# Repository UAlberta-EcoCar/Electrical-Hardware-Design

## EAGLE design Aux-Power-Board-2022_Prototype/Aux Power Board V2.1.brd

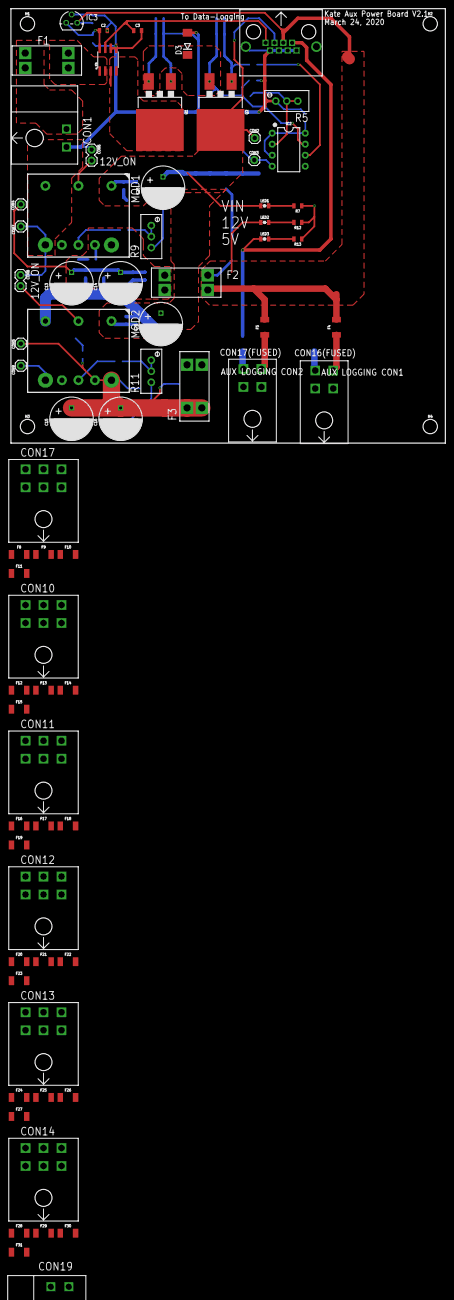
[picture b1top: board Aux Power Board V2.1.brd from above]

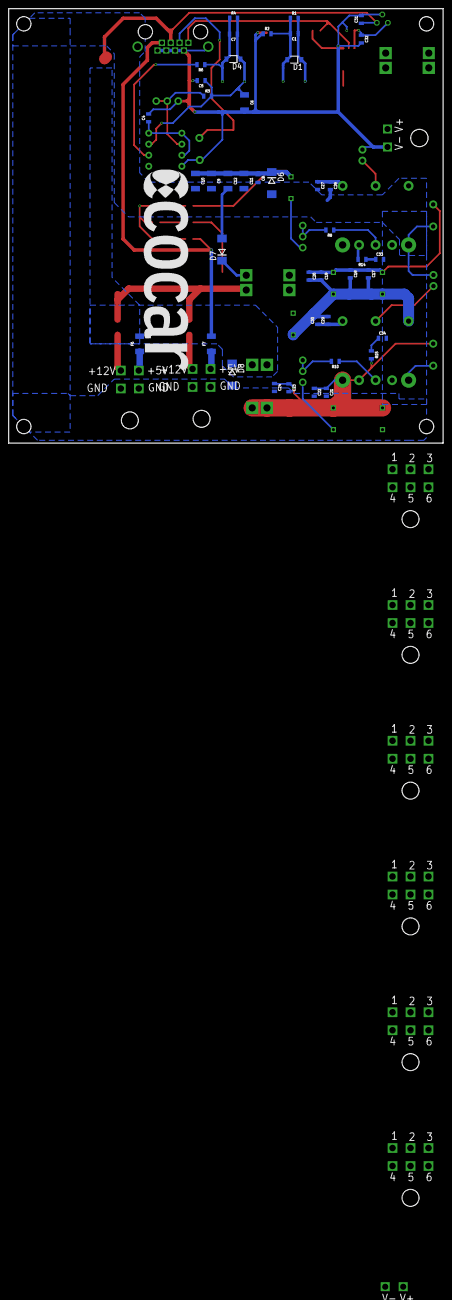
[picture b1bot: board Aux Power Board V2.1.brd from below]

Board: 2 copper layers, 100.0 x 100.0 mm, 120 parts (43 on the bottom side), 56 nets.

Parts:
C1, C2, C5, C7, C8, C17, C21: 0.1uF; 0805
C3: 1nF; 0805
C4, C31, C32: 1uF; 0805
C6, C9, C10, C11, C12: 10uF; 1210
C13, C14, C15, C16, C25, C26: 220uF; CAPACITOR_220UF_63V
C18, C19, C20, C22, C23, C24: 10uF; 0805
C27, C29: 1nF/50V; 0805
C28, C30: 1uF/50V; 0805
C33, C34: 0805
CON1, CON19: TE_2-PIN
CON2, CON3, CON4, CON5, CON7, CON9: 1X01
CON6, CON8: 1X02
CON10, CON11, CON12, CON13, CON14, CON17: TE_6-PIN
CON16(FUSED), CON17(FUSED): TE_4-PIN
CON18: RJ45
D1, D4: BZT52HC10WF-7; SOD123FL
D3, D6: SMBJ22A; DO214AA
D7: SMBJ12A; DO214AA
D8: SMBJ5.0A; DO214AA
F1, F2, F3: 7.5A; FUSEHOLDER_VERTICAL
F4, F5, F6, F7, F8, F9, F10, F11, F12, F13, F14, F15, F16, F17, F18, F19, F20, F21, F22, F23, F24, F25, F26, F27, F28, F29, F30, F31: 1210
H1, H2, H3, H4: STAND-OFF
IC1: CURRENT-SENSOR_ACS723; SOIC8
IC2: OP-AMP_LM10; DIP08
IC3: LINEAR-REGULATOR_LP2950; TO92
LED1, LED2, LED3: RED; 0805_LED
MOD1, MOD2: i3A; CONVERTER_I3A
Q1, Q2: TO-263/D2PAK
R1, R3, R4: 100k; 0805
R2, R6: 2.7k; 0805
R5, R9, R11: 10k; TRIMPOT
R7: 3.9k; 0805
R8: 1.6k; 0805
R10: 8.2k; 0805
R12: 2k; 0805
R13: 560; 0805
R14, R15: 0805
U$7: ECOCAR_LOGO; ECOCAR_LOGO_2018

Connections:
5V: CON18.7, CON19.1, D8.C, F3.3, F3.4, F6.2, F7.2, F8.2, F9.2, F12.2, F13.2, F16.2, F17.2, F20.2, F21.2, F24.2, F25.2, F28.2, F29.2, LED3.1
5V_LINEAR: C2.1, C32.1, IC1.8, IC3.3
5V_PRE_FUSE: C15.+, C16.+, C21.1, C22.1, C23.1, C24.1, CON5.1, F3.1, F3.2, MOD2.7, MOD2.8, R15.2
12V: C31.1, CON18.5, D7.C, F2.3, F2.4, F4.2, F5.2, F10.2, F11.2, F14.2, F15.2, F18.2, F19.2, F22.2, F23.2, F26.2, F27.2, F30.2, F31.2, IC3.1, LED2.1
12V_PRE_FUSE: C13.+, C14.+, C17.1, C18.1, C19.1, C20.1, CON4.1, F2.1, F2.2, MOD1.7, MOD1.8, R14.2
!OUTPUT_ENABLED: IC2.6, R6.2
+5V: CON17.6, F9.1
+5V1: CON10.6, F13.1
+5V2: CON11.6, F17.1
+5V3: CON12.6, F21.1
+5V4: CON13.6, F25.1
+5V5: CON14.6, F29.1
+12V: CON17.1, F11.1
+12V1: CON10.1, F15.1
+12V2: CON11.1, F19.1
+12V3: CON12.1, F23.1
+12V4: CON13.1, F27.1
+12V5: CON14.1, F31.1
BATTERY_IN: CON1.1, F1.1, F1.2
CURRENT_SENSOR_IN: F1.3, F1.4, IC1.1, IC1.2
CURRENT_SENSOR_OUT: IC1.3, IC1.4, Q1.2
GND: C2.2, C3.2, C4.2, C5.2, C6.2, C8.2, C9.2, C10.2, C11.2, C12.2, C13.-, C14.-, C15.-, C16.-, C17.2, C18.2, C19.2, C20.2, C21.2, C22.2, C23.2, C24.2, C25.-, C26.-, C27.2, C28.2, C29.2, C30.2, C31.2, C32.2, C33.2, C34.2, CON1.2, CON3.1, CON6.1, CON7.1, CON8.1, CON9.1, CON10.2, CON10.5, CON11.2, CON11.5, CON12.2, CON12.5, CON13.2, CON13.5, CON14.2, CON14.5, CON16(FUSED).3, CON16(FUSED).4, CON17.2, CON17.5, CON17(FUSED).3, CON17(FUSED).4, CON18.2, CON18.4, CON18.6, CON18.8, CON18.9, CON18.10, CON19.2, D3.A, D6.A, D7.A, D8.A, IC1.5, IC1.6, IC2.4, IC3.2, MOD1.3, MOD1.4, MOD2.3, MOD2.4, R2.1, R5.1, R7.1, R9.3, R11.3, R12.1, R13.1
HALL_CURRENT: C3.1, CON18.1, IC1.7
unnamed: CON16(FUSED).2, F6.1
unnamed: CON16(FUSED).1, F4.1
unnamed: MOD1.6, R8.1
unnamed: LED1.2, R7.2
unnamed: C4.1, IC2.1, IC2.3, IC2.8
unnamed: IC2.2, R3.1, R5.2, R5.3
unnamed: R8.2, R9.1, R9.2
unnamed: C7.2, D4.A, Q2.1, R4.1, R6.1
unnamed: C33.1, R14.1
unnamed: CON17(FUSED).1, F5.1
unnamed: MOD2.6, R10.1
unnamed: CON17(FUSED).2, F7.1
unnamed: LED3.2, R13.2
unnamed: C1.2, D1.A, Q1.1, R1.1, R2.2
unnamed: C34.1, R15.1
unnamed: CON10.3, F14.1
unnamed: LED2.2, R12.2
unnamed: CON17.3, F10.1
unnamed: CON10.4, F12.1
unnamed: CON17.4, F8.1
unnamed: CON11.3, F18.1
unnamed: CON11.4, F16.1
unnamed: CON12.3, F22.1
unnamed: CON12.4, F20.1
unnamed: CON13.3, F26.1
unnamed: R10.2, R11.1, R11.2
unnamed: CON13.4, F24.1
unnamed: CON14.3, F30.1
unnamed: CON14.4, F28.1
unnamed: CON6.2, MOD1.2
unnamed: CON8.2, MOD2.2
REVERSE_PROT_OUT: C1.1, C5.1, C6.1, C7.1, D1.C, D3.C, D4.C, IC2.7, Q1.3, Q2.3, R1.2, R3.2, R4.2
VIN: C8.1, C9.1, C10.1, C11.1, C12.1, C25.+, C26.+, C27.1, C28.1, C29.1, C30.1, CON2.1, CON18.3, D6.C, LED1.1, MOD1.1, MOD2.1, Q2.2

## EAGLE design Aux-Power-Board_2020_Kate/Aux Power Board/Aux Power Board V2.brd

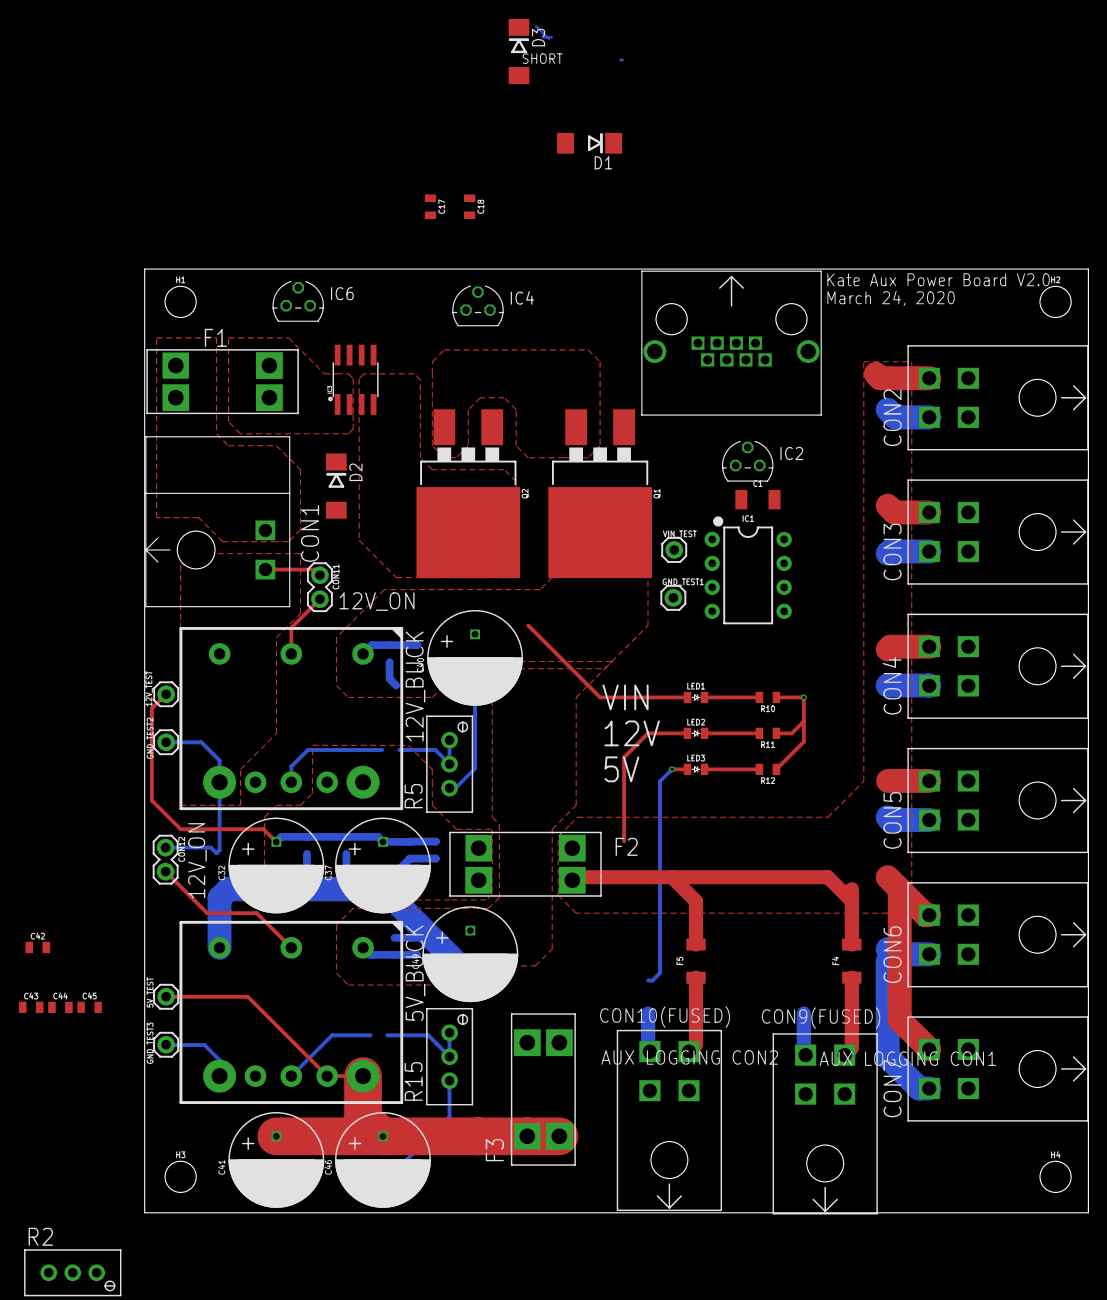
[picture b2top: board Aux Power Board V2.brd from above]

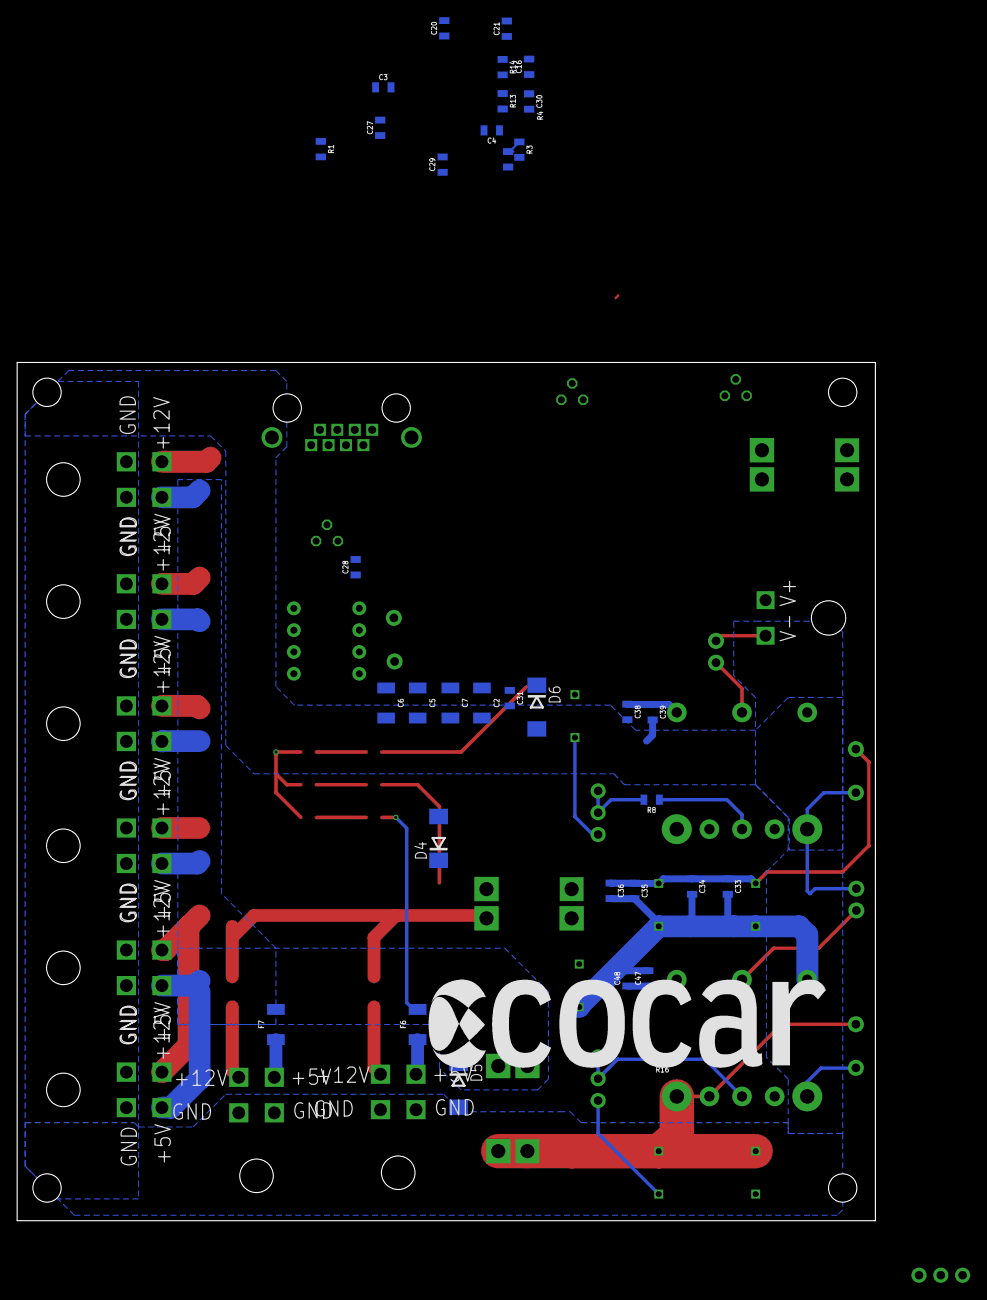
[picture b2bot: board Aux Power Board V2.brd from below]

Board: 2 copper layers, 100.0 x 100.0 mm, 96 parts (35 on the bottom side), 32 nets.

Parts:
5V_BUCK, 12V_BUCK: i3A; CONVERTER_I3A
5V_TEST, 12V_TEST: 1X01
AUX_LOGGING: RJ45
C1, C2, C5, C6, C7: 10uF; 1210
C3, C4, C16, C21: 1uF; 0805
C17, C20, C27, C28, C29, C30, C31, C33, C42: 0.1uF; 0805
C18: 1nF; 0805
C32, C37, C40, C41, C46, C49: 220uF; CAPACITOR_220UF_63V
C34, C35, C36, C43, C44, C45: 10uF; 0805
C38, C47: 1nF/50V; 0805
C39, C48: 1uF/50V; 0805
CON1: TE_2-PIN
CON2, CON3, CON4, CON5, CON6, CON7, CON9(FUSED), CON10(FUSED): TE_4-PIN
CON11, CON12: 1X02
D1, D3, D4: SMBJ12CA; DO214AA
D2, D6: SMBJ22CA; DO214AA
D5: SMBJ5.0CA; DO214AA
F1, F2, F3: 7.5A; FUSEHOLDER_VERTICAL
F4, F5, F6, F7: 1210
GND_TEST1, GND_TEST2, GND_TEST3: 1X01
H1, H2, H3, H4: STAND-OFF
IC1: OP-AMP_LM10; DIP08
IC2, IC4: LINEAR-REGULATOR_LM337L; TO92
IC3: CURRENT-SENSOR_ACS723; SOIC8
IC6: LINEAR-REGULATOR_LP2950; TO92
LED1, LED2, LED3: RED; 0805_LED
Q1, Q2: TO-263/D2PAK
R1: 100k; 0805
R2, R5, R15: 10k; TRIMPOT
R3, R13: 2.4k; 0805
R4, R14: 330; 0805
R8: 1.6k; 0805
R10: 3.9k; 0805
R11: 2k; 0805
R12: 560; 0805
R16: 8.2k; 0805
U$7: ECOCAR_LOGO; ECOCAR_LOGO_2018
VIN_TEST: 1X01

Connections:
5V: AUX_LOGGING.7, CON2.2, CON3.2, CON4.2, CON5.2, CON6.2, CON7.2, D5.C, F3.3, F3.4, F6.2, F7.2, LED3.1
5V_LINEAR: C17.1, C21.1, IC3.8, IC6.3
12V: AUX_LOGGING.5, C20.1, CON2.1, CON3.1, CON4.1, CON5.1, CON6.1, CON7.1, D4.C, F2.3, F2.4, F4.2, F5.2, IC6.1, LED2.1
BATTERY_IN: CON1.1, F1.1, F1.2
CURRENT_SENSOR_IN: F1.3, F1.4, IC3.1, IC3.2
CURRENT_SENSOR_OUT: D2.C, IC3.3, IC3.4, Q2.2
GND: 5V_BUCK.3, 5V_BUCK.4, 12V_BUCK.3, 12V_BUCK.4, AUX_LOGGING.2, AUX_LOGGING.4, AUX_LOGGING.6, AUX_LOGGING.8, AUX_LOGGING.9, AUX_LOGGING.10, C1.2, C2.2, C3.2, C5.2, C6.2, C7.2, C17.2, C18.2, C20.2, C21.2, C27.2, C28.2, C29.2, C30.2, C31.2, C32.-, C33.2, C34.2, C35.2, C36.2, C37.-, C38.2, C39.2, C40.-, C41.-, C42.2, C43.2, C44.2, C45.2, C46.-, C47.2, C48.2, C49.-, CON1.2, CON2.3, CON2.4, CON3.3, CON3.4, CON4.3, CON4.4, CON5.3, CON5.4, CON6.3, CON6.4, CON7.3, CON7.4, CON9(FUSED).3, CON9(FUSED).4, CON10(FUSED).3, CON10(FUSED).4, CON11.1, CON12.1, D2.A, D4.A, D5.A, D6.A, GND_TEST1.1, GND_TEST2.1, GND_TEST3.1, IC1.4, IC3.5, IC3.6, IC4.1, IC6.2, R2.1, R5.3, R10.1, R11.1, R12.1, R15.3
HALL_CURRENT: AUX_LOGGING.1, C18.1, IC3.7
unnamed: CON9(FUSED).2, F7.1
unnamed: CON9(FUSED).1, F4.1
unnamed: 12V_BUCK.6, R8.1
unnamed: LED1.2, R10.2
unnamed: C3.1, IC1.1, IC1.3, IC1.8
unnamed: C27.1, IC1.2, R1.1, R2.2, R2.3
unnamed: R5.1, R5.2, R8.2
unnamed: C4.2, D3.A, IC2.2, Q1.1, R4.1
unnamed: IC2.3, R3.1, R4.2
unnamed: CON10(FUSED).1, F5.1
unnamed: 5V_BUCK.6, R16.1
unnamed: CON10(FUSED).2, F6.1
unnamed: LED3.2, R12.2
unnamed: LED2.2, R11.2
unnamed: IC4.3, R13.1, R14.2
unnamed: C16.2, D1.A, IC4.2, Q2.1, R14.1
unnamed: 12V_BUCK.7, 12V_BUCK.8, 12V_TEST.1, C32.+, C33.1, C34.1, C35.1, C36.1, C37.+, F2.1, F2.2
unnamed: R15.1, R15.2, R16.2
unnamed: 5V_BUCK.7, 5V_BUCK.8, 5V_TEST.1, C41.+, C42.1, C43.1, C44.1, C45.1, C46.+, F3.1, F3.2
unnamed: 12V_BUCK.2, CON11.2
unnamed: 5V_BUCK.2, CON12.2
REGULATOR_ON: C29.1, IC1.6, IC2.1
REVERSE_PROT_OUT: C1.1, C4.1, C16.1, C28.1, C30.1, D1.C, D3.C, IC1.7, Q1.3, Q2.3, R1.2, R3.2, R13.2
VIN: 5V_BUCK.1, 12V_BUCK.1, AUX_LOGGING.3, C2.1, C5.1, C6.1, C7.1, C31.1, C38.1, C39.1, C40.+, C47.1, C48.1, C49.+, D6.C, LED1.1, Q1.2, VIN_TEST.1

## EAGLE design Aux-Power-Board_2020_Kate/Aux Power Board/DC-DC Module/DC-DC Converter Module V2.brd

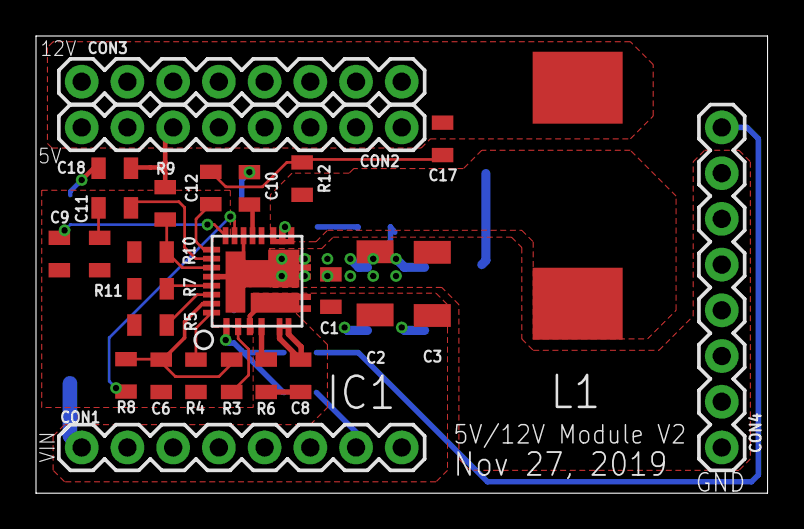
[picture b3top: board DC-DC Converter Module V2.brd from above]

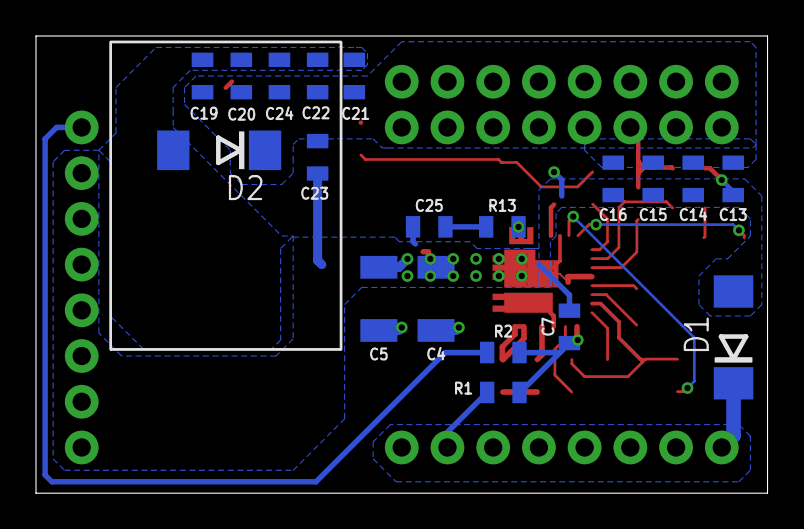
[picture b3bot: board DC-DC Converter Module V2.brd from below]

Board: 2 copper layers, 40.6 x 25.4 mm, 47 parts (19 on the bottom side), 24 nets.

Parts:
C1, C7, C18: 0.1uF/50V; 0805
C2, C3, C4, C5: 10uF/50V; 1210
C6, C8: 1uF; 0805
C9, C11, C12, C17, C25: 0805
C10: 4.7uF/25V; 0805
C13, C14, C15, C16, C19, C20, C21, C22, C23, C24: 22uF/25V; 0805
CON1, CON2, CON3, CON4: 1X08
D1, D2: DO214AA
IC1: BUCK_SIC472; MLP55-27L
J1: AGND_JUMPER_MLP55
L1: 10uH; INDUCTOR_BOURNS_SRP1265A
R1, R2, R8: 0; 0805
R3: 100k; 0805
R4: 300k; 0805
R5: 62k; 0805
R6: 3.3; 0805
R7: 180k/82k; 0805
R9, R10, R11, R12, R13: 0805

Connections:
5V: CON4.8, R2.1
AGND: C6.2, C9.1, IC1.23, IC1.28, J1.P$2, R4.2, R5.1, R7.1, R10.2, R11.2
COMP: C11.2, IC1.21
FEEDBACK: IC1.22, R9.1, R10.1
GND: C1.1, C2.2, C3.2, C4.2, C5.2, C7.2, C10.2, C13.1, C14.1, C15.1, C16.1, C18.1, C19.1, C20.1, C21.1, C22.1, C23.1, C24.1, C25.1, CON4.1, CON4.2, CON4.3, CON4.4, CON4.5, CON4.6, CON4.7, D1.A, D2.A, IC1.9/10/11/30, IC1.17, J1.P$1
MODE: IC1.27, R4.1
unnamed: IC1.2, R3.1
unnamed: C11.1, R11.1
unnamed: C10.1, IC1.16
unnamed: IC1.18, R8.2
unnamed: IC1.4, R6.1
unnamed: C8.2, IC1.5, IC1.6
unnamed: C8.1, R6.2
unnamed: C9.2, IC1.19
unnamed: IC1.24, R7.2
unnamed: IC1.25, R5.2
unnamed: C25.2, R13.1
unnamed: C12.2, C17.2, R12.2
SW: IC1.12/13/14, L1.1, R12.1, R13.2
VCC: C13.2, C14.2, C15.2, C16.2, C17.1, C18.2, C19.2, C20.2, C21.2, C22.2, C23.2, C24.2, CON2.1, CON2.2, CON2.3, CON2.4, CON2.5, CON2.6, CON2.7, CON2.8, CON3.1, CON3.2, CON3.3, CON3.4, CON3.5, CON3.6, CON3.7, CON3.8, D2.C, L1.2, R9.2
VCIN: C7.1, IC1.1, R1.2, R2.2
VDD: C6.1, IC1.26, R3.2, R8.1
VIN: C1.2, C2.1, C3.1, C4.1, C5.1, CON1.1, CON1.2, CON1.3, CON1.4, CON1.5, CON1.6, CON1.7, CON1.8, D1.C, IC1.3, IC1.7/8, R1.1
VSNS: C12.1, IC1.20

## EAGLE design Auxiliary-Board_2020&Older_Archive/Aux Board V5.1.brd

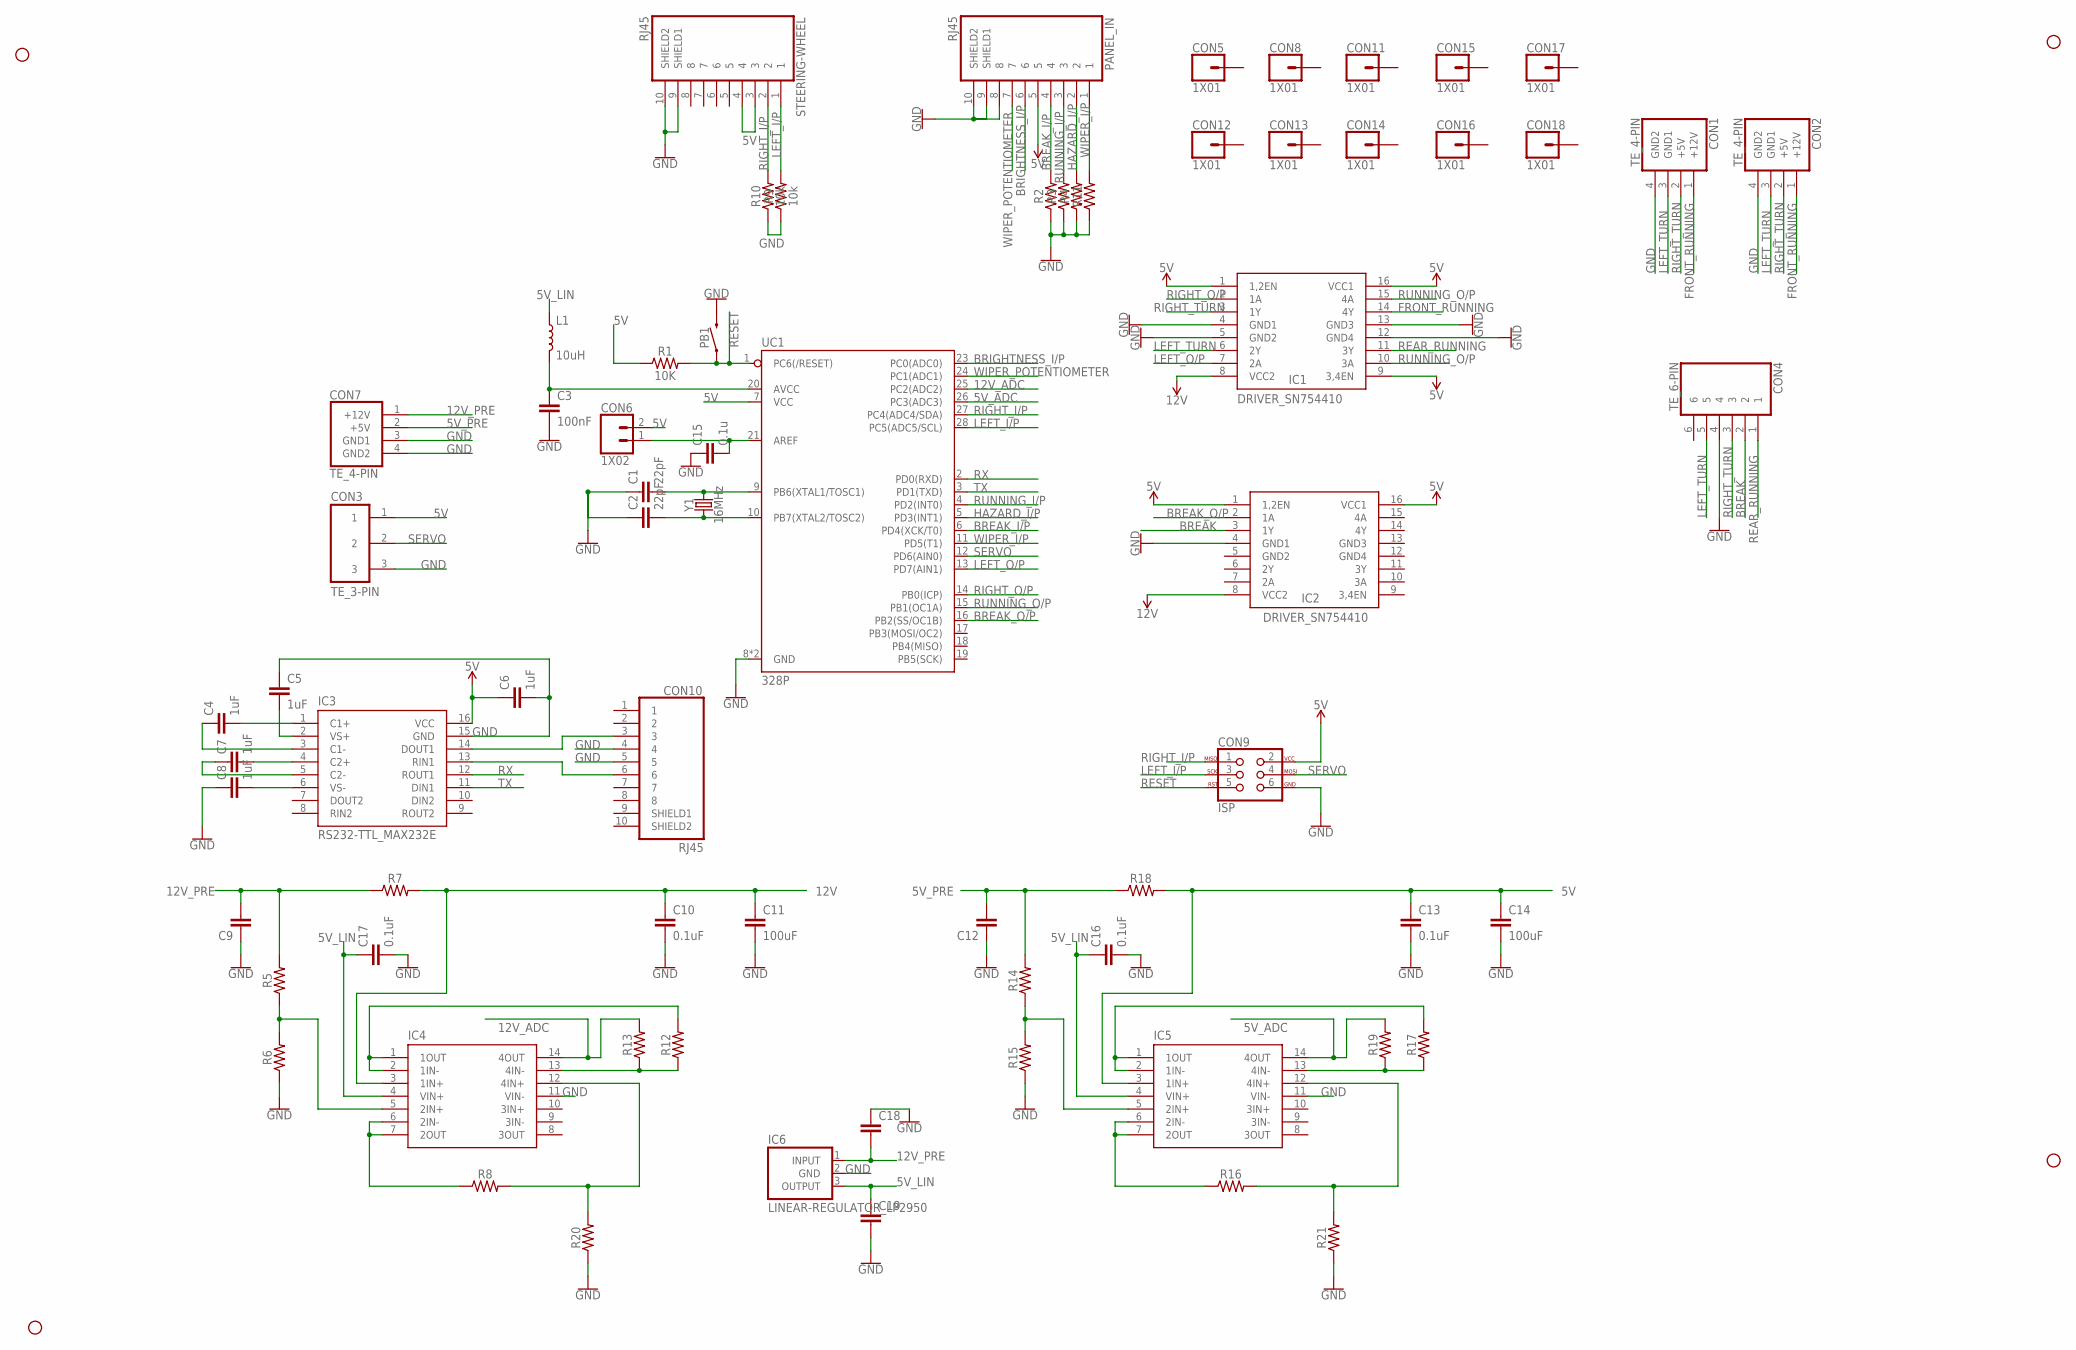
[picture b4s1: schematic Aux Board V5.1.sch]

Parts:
C1, C2: 22pF; 0805
C3: 100nF; 0805
C4, C5, C6, C7, C8: 1uF; 0805
C9, C12, C18, C19: CAPACITOR_0805; 0805
C10, C13, C16, C17: 0.1uF; 0805
C11, C14: 100uF; 0805
C15: 0.1u; 0805
CON1, CON2, CON7: TE_4-PIN
CON3: TE_3-PIN
CON4: TE_6-PIN
CON5, CON8, CON11, CON12, CON13, CON14, CON15, CON16, CON17, CON18: 1X01
CON6: 1X02
CON9: ISP; ISP_CONNECTOR
CON10: RJ45
H1, H2, H3, H4: STAND-OFF
IC1, IC2: DRIVER_SN754410; DIP16
IC3: RS232-TTL_MAX232E; DIP16
IC4, IC5: OP-AMP_QUAD; DIP14
IC6: LINEAR-REGULATOR_LP2950; TO92
L1: 10uH; 0805
PANEL_IN: RJ45
PB1: PUSHBUTTON
R1: 10K; 0805
R2, R3, R4, R5, R6, R8, R11, R12, R13, R14, R15, R16, R17, R19, R20, R21: RESISTOR_0805; 0805
R7, R18: RESISTOR_1210; 1210
R9, R10: 10k; 0805
STEERING-WHEEL: RJ45
UC1: 328P; DIP28
Y1: 16MHz; HC49US

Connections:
5V: C6.1, C13.1, C14.1, C15.2, CON3.1, CON6.1, CON6.2, CON9.2, IC1.1 (1,2EN), IC1.9 (3,4EN), IC1.16 (VCC1), IC2.1 (1,2EN), IC2.16 (VCC1), IC3.16 (VCC), IC5.3 (1IN+), PANEL_IN.5, R1.1, R18.2, STEERING-WHEEL.3, STEERING-WHEEL.4, UC1.7 (VCC), UC1.21 (AREF)
5V_ADC: IC5.14 (4OUT), R19.2, UC1.26 (PC3(ADC3))
5V_LIN: C16.1, C17.1, C19.1, IC4.4 (VIN+), IC5.4 (VIN+), IC6.3 (OUTPUT), L1.1
5V_PRE: C12.2, CON7.2 (+5V), R14.2, R18.1
12V: C10.1, C11.1, IC1.8 (VCC2), IC2.8 (VCC2), IC4.3 (1IN+), R7.2
12V_ADC: IC4.14 (4OUT), R13.2, UC1.25 (PC2(ADC2))
12V_PRE: C9.2, C18.2, CON7.1 (+12V), IC6.1 (INPUT), R5.2, R7.1
BREAK: CON4.2, IC2.3 (1Y)
BREAK_I/P: PANEL_IN.4, R2.2, UC1.6 (PD4(XCK/T0))
BREAK_O/P: IC2.2 (1A), UC1.16 (PB2(SS/OC1B))
BRIGHTNESS_I/P: PANEL_IN.6, UC1.23 (PC0(ADC0))
FRONT_RUNNING: CON1.1 (+12V), CON2.1 (+12V), IC1.14 (4Y)
GND: C1.1, C2.1, C3.2, C5.1, C6.2, C8.1, C9.1, C10.2, C11.2, C12.1, C13.2, C14.2, C15.1, C16.2, C17.2, C18.1, C19.2, CON1.4 (GND2), CON2.4 (GND2), CON3.3, CON4.4, CON7.3 (GND1), CON7.4 (GND2), CON9.6, CON10.4, CON10.5, IC1.4 (GND1), IC1.5 (GND2), IC1.12 (GND4), IC1.13 (GND3), IC2.4 (GND1), IC3.15 (GND), IC4.11 (VIN-), IC5.11 (VIN-), IC6.2 (GND), PANEL_IN.8, PANEL_IN.9 (SHIELD1), PANEL_IN.10 (SHIELD2), PB1.3 (2), PB1.4 (2), R2.1, R3.1, R4.1, R6.1, R9.1, R10.1, R11.1, R15.1, R20.1, R21.1, STEERING-WHEEL.9 (SHIELD1), STEERING-WHEEL.10 (SHIELD2), UC1.8 (GND), UC1.22 (GND)
HAZARD_I/P: PANEL_IN.2, R4.2, UC1.5 (PD3(INT1))
LEFT_I/P: CON9.3, R9.2, STEERING-WHEEL.1, UC1.28 (PC5(ADC5/SCL))
LEFT_O/P: IC1.7 (2A), UC1.13 (PD7(AIN1))
LEFT_TURN: CON1.3 (GND1), CON2.3 (GND1), CON4.5, IC1.6 (2Y)
unnamed: C4.2, IC3.1 (C1+)
unnamed: IC4.5 (2IN+), R5.1, R6.2
unnamed: C4.1, IC3.3 (C1-)
unnamed: C5.2, IC3.2 (VS+)
unnamed: IC4.6 (2IN-), IC4.7 (2OUT), R8.1
unnamed: IC5.5 (2IN+), R14.1, R15.2
unnamed: IC4.1 (1OUT), IC4.2 (1IN-), R12.2
unnamed: C1.2, UC1.9 (PB6(XTAL1/TOSC1)), Y1.2
unnamed: C2.2, UC1.10 (PB7(XTAL2/TOSC2)), Y1.1
unnamed: C7.2, IC3.4 (C2+)
unnamed: C7.1, IC3.5 (C2-)
unnamed: C8.2, IC3.6 (VS-)
unnamed: CON10.3, IC3.14 (DOUT1)
unnamed: CON10.6, IC3.13 (RIN1)
unnamed: IC4.13 (4IN-), R12.1, R13.1
unnamed: IC5.6 (2IN-), IC5.7 (2OUT), R16.1
unnamed: IC5.1 (1OUT), IC5.2 (1IN-), R17.2
unnamed: IC5.13 (4IN-), R17.1, R19.1
unnamed: C3.1, L1.2, UC1.20 (AVCC)
unnamed: IC4.12 (4IN+), R8.2, R20.2
unnamed: IC5.12 (4IN+), R16.2, R21.2
REAR_RUNNING: CON4.1, IC1.11 (3Y)
RESET: CON9.5, PB1.1, PB1.2 (1), R1.2, UC1.1 (PC6(/RESET))
RIGHT_I/P: CON9.1, R10.2, STEERING-WHEEL.2, UC1.27 (PC4(ADC4/SDA))
RIGHT_O/P: IC1.2 (1A), UC1.14 (PB0(ICP))
RIGHT_TURN: CON1.2 (+5V), CON2.2 (+5V), CON4.3, IC1.3 (1Y)
RUNNING_I/P: PANEL_IN.3, R3.2, UC1.4 (PD2(INT0))
RUNNING_O/P: IC1.10 (3A), IC1.15 (4A), UC1.15 (PB1(OC1A))
RX: IC3.12 (ROUT1), UC1.2 (PD0(RXD))
SERVO: CON3.2, CON9.4, UC1.12 (PD6(AIN0))
TX: IC3.11 (DIN1), UC1.3 (PD1(TXD))
WIPER_I/P: PANEL_IN.1, R11.2, UC1.11 (PD5(T1))
WIPER_POTENTIOMETER: PANEL_IN.7, UC1.24 (PC1(ADC1))

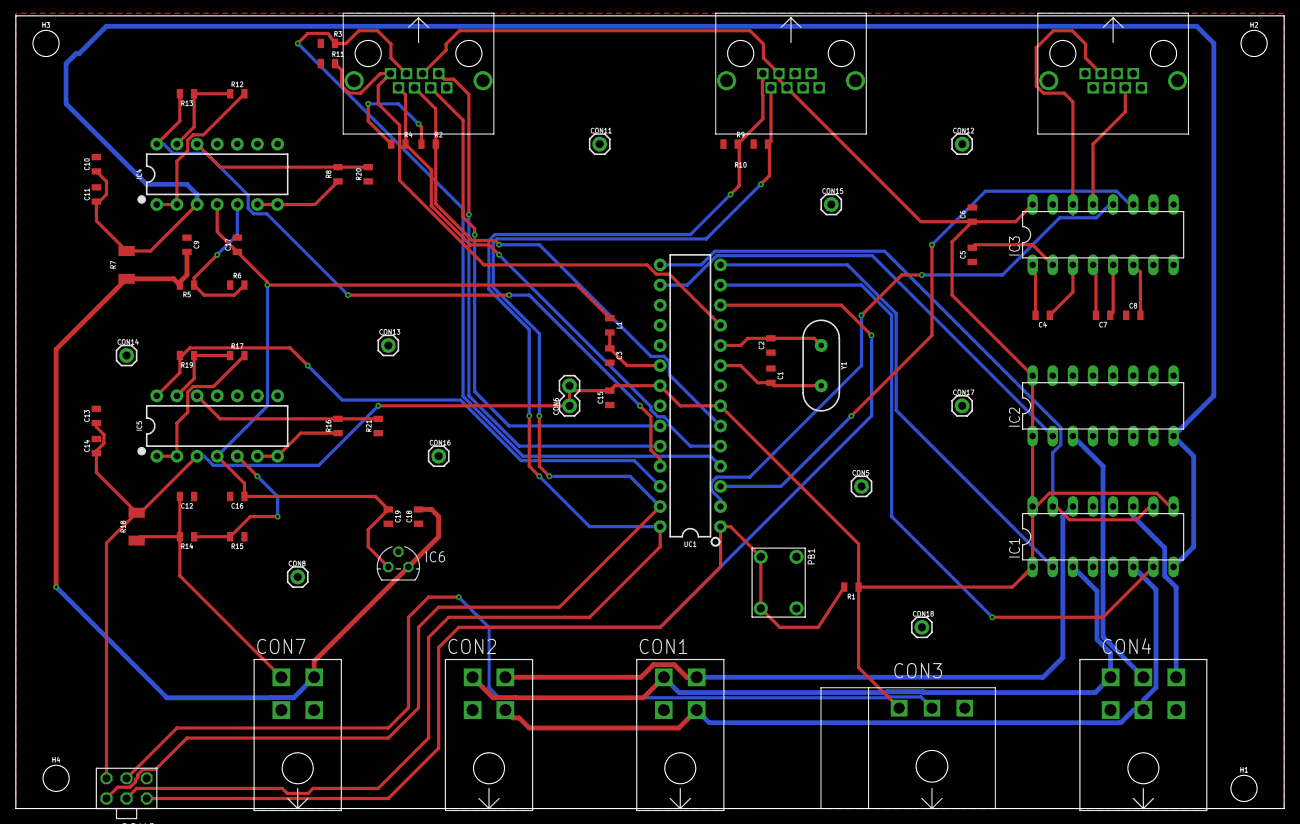
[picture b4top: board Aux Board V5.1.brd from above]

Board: 2 copper layers, 160.0 x 100.0 mm, 74 parts (0 on the bottom side), 50 nets.

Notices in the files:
parts and their libraries:
SparkFun-PowerSymbols: Licensing: Creative Commons ShareAlike 4.0 International - https://creativecommons.org/licenses/by-sa/4.0
